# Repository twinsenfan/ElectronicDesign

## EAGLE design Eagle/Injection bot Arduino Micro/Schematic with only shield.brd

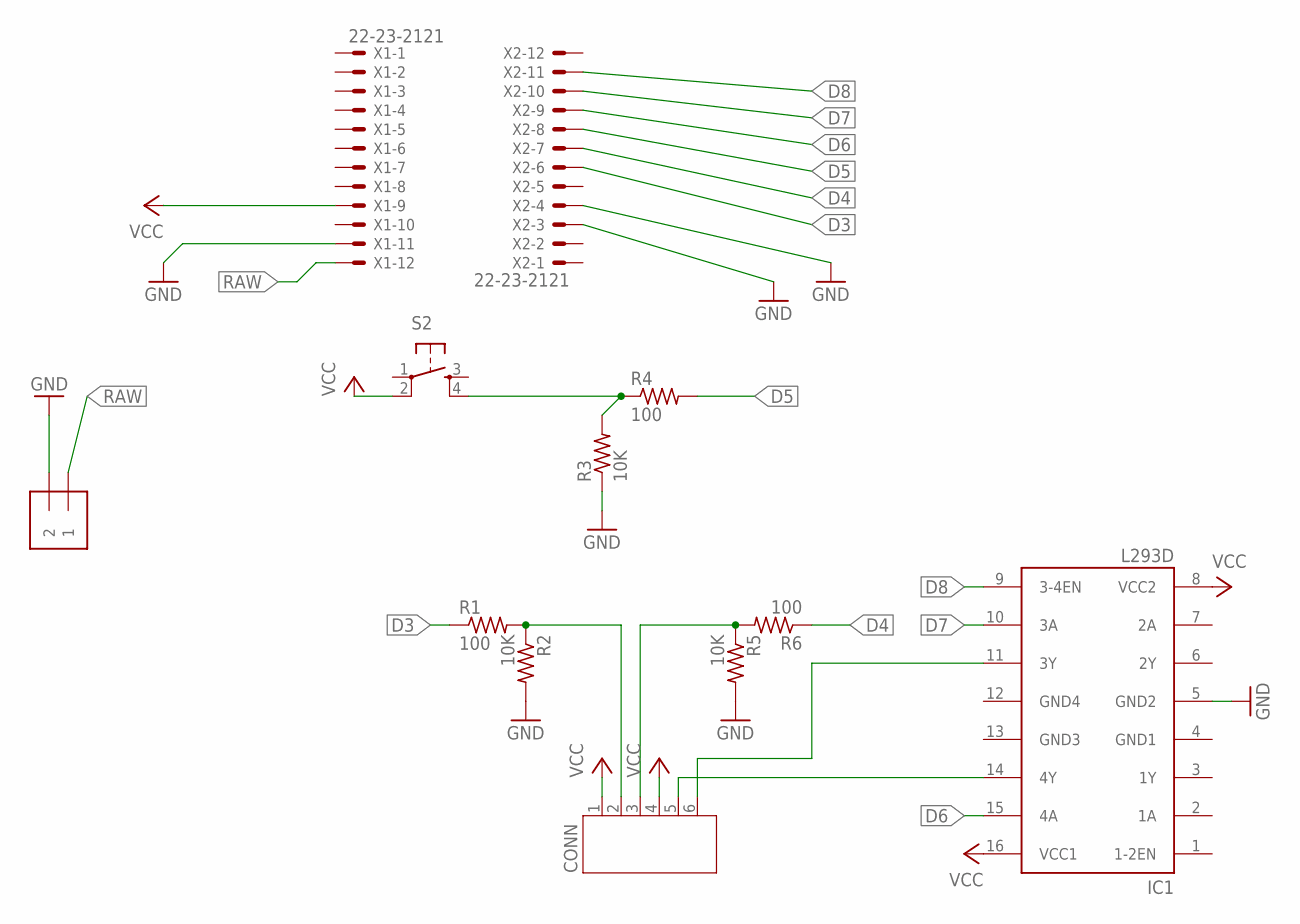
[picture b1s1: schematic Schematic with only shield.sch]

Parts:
CONN: JST-PH6
IC1: L293D; DIL16; MPN L293DNEE4
J1: 1X2-3.5MM
R1, R4, R6: 100; 0204/7; MPN 0-65-425
R2, R3, R5: 10K; 0204/7
S2: TAC_SWITCHPTH; TACTILE-PTH
X1, X2: 22-23-2121

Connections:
D3: R1.1, X2.6
D4: R6.1, X2.7
D5: R4.2, X2.8
D6: IC1.15 (4A), X2.9
D7: IC1.10 (3A), X2.10
D8: IC1.9 (3-4EN), X2.11
GND: IC1.5 (GND2), J1.2, R2.2, R3.1, R5.2, X1.11, X2.3, X2.4
GND1: IC1.4 (GND1)
GND3: IC1.13 (GND3)
GND4: IC1.12 (GND4)
unnamed: R3.2, R4.1, S2.4
unnamed: CONN.3, R5.1, R6.2
unnamed: CONN.2, R1.2, R2.1
unnamed: CONN.6, IC1.11 (3Y)
unnamed: CONN.5, IC1.14 (4Y)
RAW: J1.1, X1.12
VCC: CONN.1, CONN.4, IC1.8 (VCC2), IC1.16 (VCC1), S2.2, X1.9

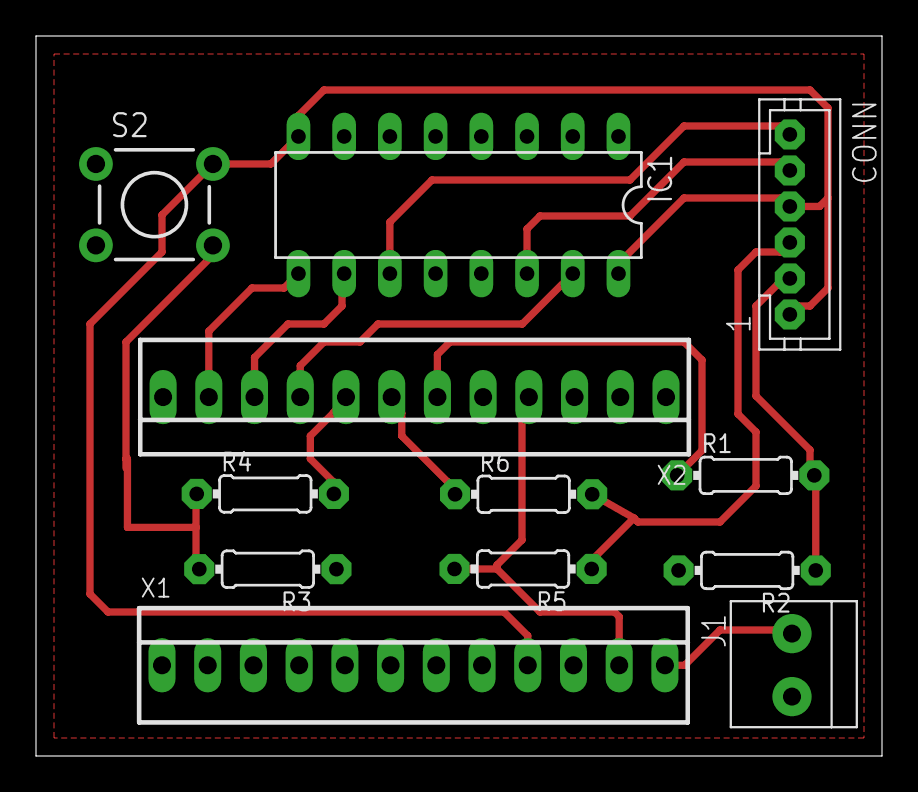
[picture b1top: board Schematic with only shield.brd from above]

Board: 2 copper layers, 47.0 x 40.0 mm, 12 parts (0 on the bottom side), 14 nets.

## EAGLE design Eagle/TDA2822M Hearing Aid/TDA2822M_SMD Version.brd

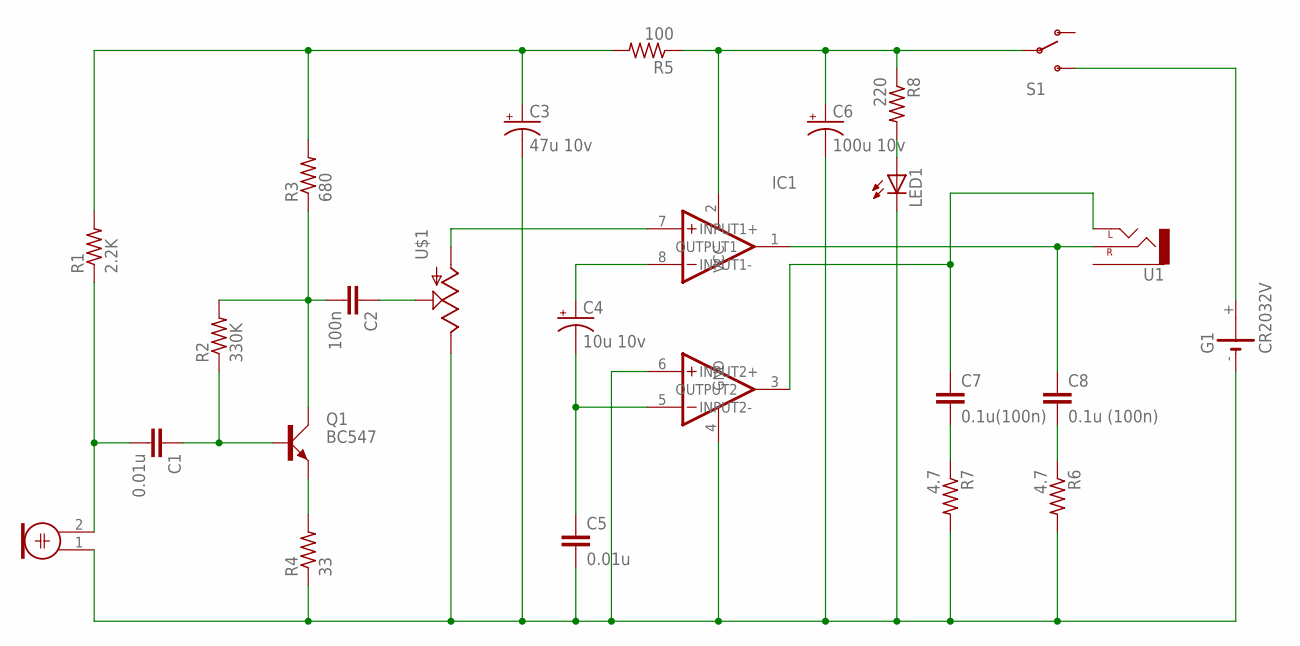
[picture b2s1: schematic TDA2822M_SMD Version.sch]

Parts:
C1, C5: 0.01u; 1206
C2: 100n; 0805
C3: 47u 10v; CPOL-RADIAL-10UF-25V
C4: 10u 10v; CPOL-RADIAL-10UF-25V
C6: 100u 10v; CPOL-RADIAL-10UF-25V
C7: 0.1u(100n); 1206
C8: 0.1u (100n); 1206
G1: CR2032V
IC1: TDA2822M; DIL8
LED1: LED3MM
M1: ELECTRET_MICROPHON-F6035AP; F6035AP
Q1: BC547; SOT54A
R1: 2.2K; R1206
R2: 330K; R1206
R3: 680; R1206
R4: 33; R1206
R5: 100; R1206
R6, R7: 4.7; R1206
R8: 220; R1206
S1: SWITCH-SPSTKIT; SWITCH-SPDT_KIT
U1: AUDIO-JACKPTH; AUDIO-JACK
U$1: POT-RV16AF-20; POT_ALPHA_RV16AF-20

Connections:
GND: C3.2 (-), C5.2, C6.2 (-), G1.-, IC1.4 (GND), IC1.6 (INPUT2+), LED1.K (C), M1.1, R4.1, R6.2, R7.2, U$1.3 (E)
unnamed: C3.1 (+), R1.2, R3.2, R5.2
unnamed: C2.2, Q1.C, R2.2, R3.1
unnamed: C1.2, M1.2, R1.1
unnamed: Q1.E, R4.2
unnamed: C2.1, U$1.2 (S)
unnamed: C4.2 (-), C5.1, IC1.5 (INPUT2-)
unnamed: C7.2, R7.1
unnamed: C8.2, R6.1
unnamed: LED1.A, R8.2
unnamed: C6.1 (+), IC1.2 (VCC), R5.1, R8.1, S1.2
unnamed: C8.1, IC1.1 (OUTPUT1), U1.RING (RIGHT)
unnamed: C1.1, Q1.B, R2.1
unnamed: C4.1 (+), IC1.8 (INPUT1-)
unnamed: IC1.7 (INPUT1+), U$1.1 (A)
unnamed: C7.1, IC1.3 (OUTPUT2), U1.TIP (LEFT)
VCC: G1.+, S1.3 (S)

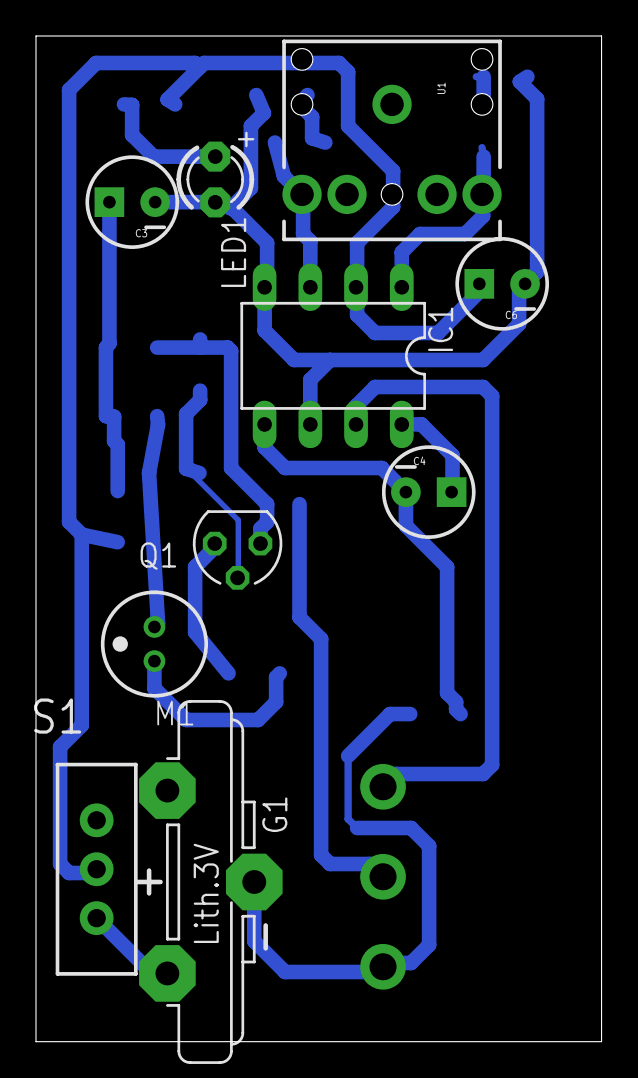
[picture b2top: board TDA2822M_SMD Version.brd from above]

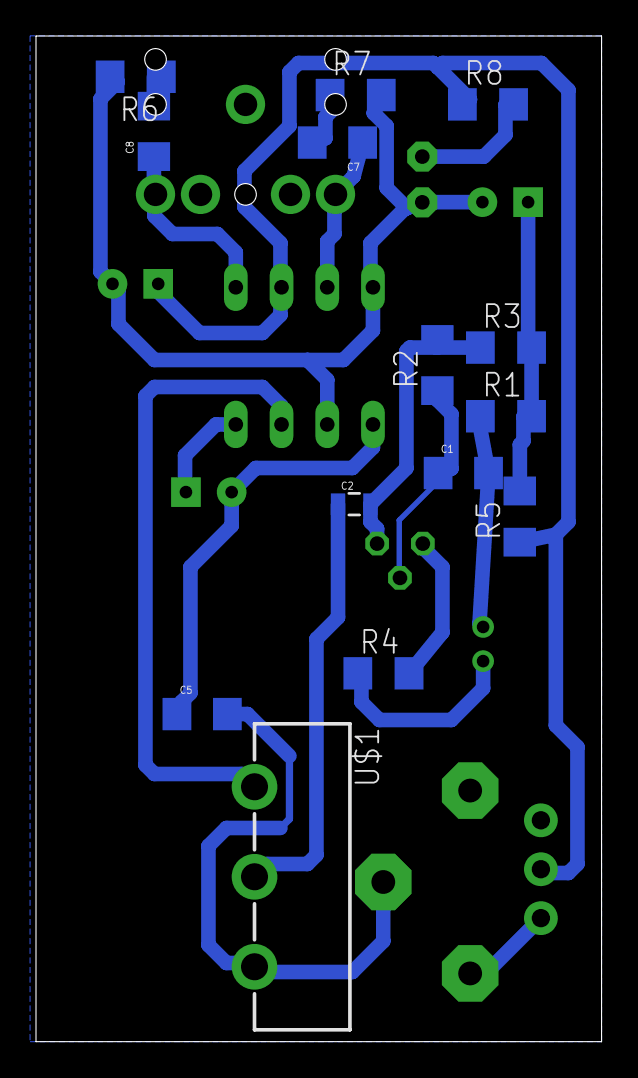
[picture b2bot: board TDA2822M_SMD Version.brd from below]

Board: 2 copper layers, 31.4 x 55.9 mm, 24 parts (14 on the bottom side), 17 nets.

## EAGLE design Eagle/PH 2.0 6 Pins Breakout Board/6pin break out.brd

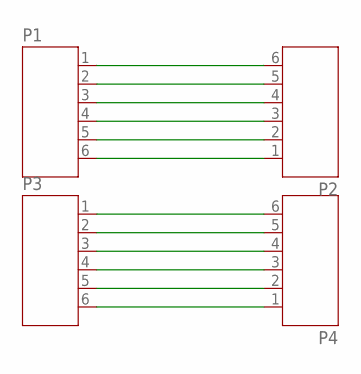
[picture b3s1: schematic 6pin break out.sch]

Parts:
P1, P2, P3, P4: JST-PH6

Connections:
unnamed: P1.1, P2.6
unnamed: P1.2, P2.5
unnamed: P1.3, P2.4
unnamed: P1.4, P2.3
unnamed: P1.5, P2.2
unnamed: P1.6, P2.1
unnamed: P3.1, P4.6
unnamed: P3.2, P4.5
unnamed: P3.3, P4.4
unnamed: P3.4, P4.3
unnamed: P3.5, P4.2
unnamed: P3.6, P4.1

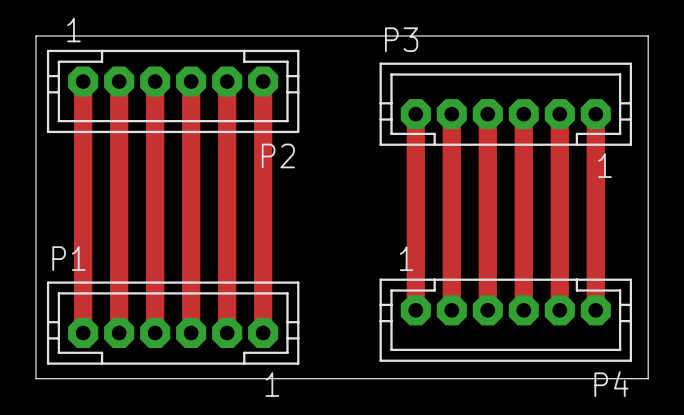
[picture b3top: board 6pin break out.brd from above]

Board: 2 copper layers, 34.0 x 19.0 mm, 4 parts (0 on the bottom side), 12 nets.

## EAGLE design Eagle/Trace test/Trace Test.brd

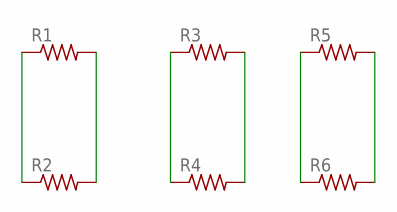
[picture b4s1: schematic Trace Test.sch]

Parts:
R1, R2, R3, R4, R5, R6: R-US_0204/5; 0204/5

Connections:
unnamed: R1.1, R2.1
unnamed: R1.2, R2.2
unnamed: R3.1, R4.1
unnamed: R3.2, R4.2
unnamed: R5.1, R6.1
unnamed: R5.2, R6.2

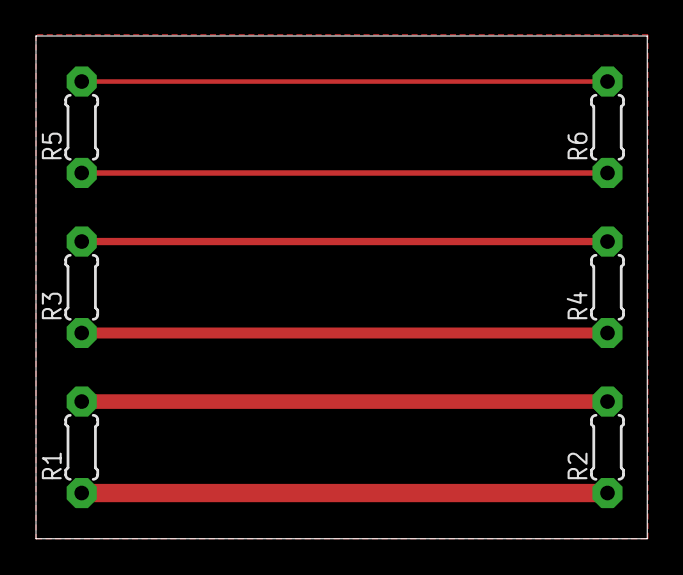
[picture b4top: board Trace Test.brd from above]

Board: 2 copper layers, 34.0 x 27.9 mm, 6 parts (0 on the bottom side), 6 nets.

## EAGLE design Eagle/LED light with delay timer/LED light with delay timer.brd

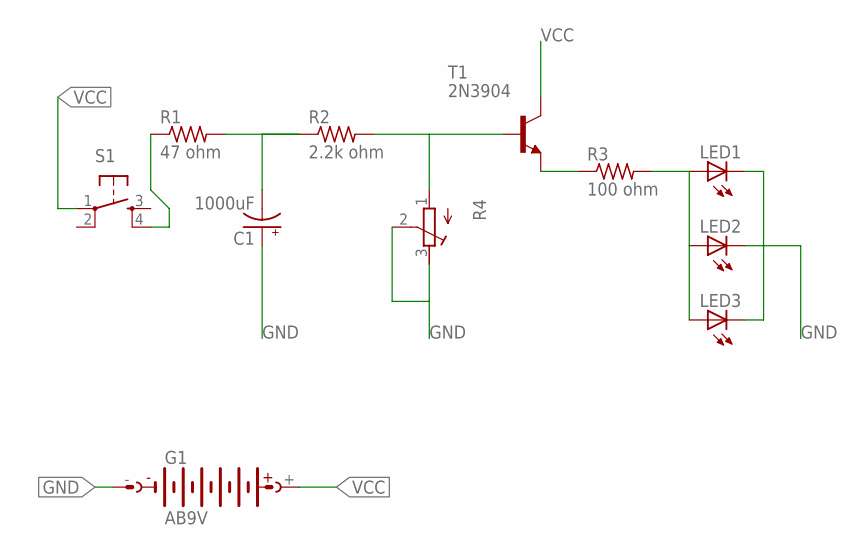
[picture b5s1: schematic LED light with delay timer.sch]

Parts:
C1: 1000uF; CPOL-RADIAL-100UF-25V
G1: AB9V
LED1, LED2, LED3: LED5MM
R1: 47 ohm; 0204/7
R2: 2.2k ohm; 0204/7
R3: 100 ohm; 0204/7
R4: R-TRIMM3339P; RTRIM3339P
S1: TAC_SWITCHPTH; TACTILE-PTH
T1: 2N3904; TO92

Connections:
GND: C1.1 (+), G1.-, LED1.K (C), LED2.K (C), LED3.K (C), R4.2 (S), R4.3 (E)
unnamed: C1.2 (-), R1.2, R2.1
unnamed: R2.2, R4.1 (A), T1.2 (B)
unnamed: R1.1, S1.4
unnamed: R3.1, T1.3 (E)
unnamed: LED1.A, LED2.A, LED3.A, R3.2
VCC: G1.+, S1.1, T1.1 (C)

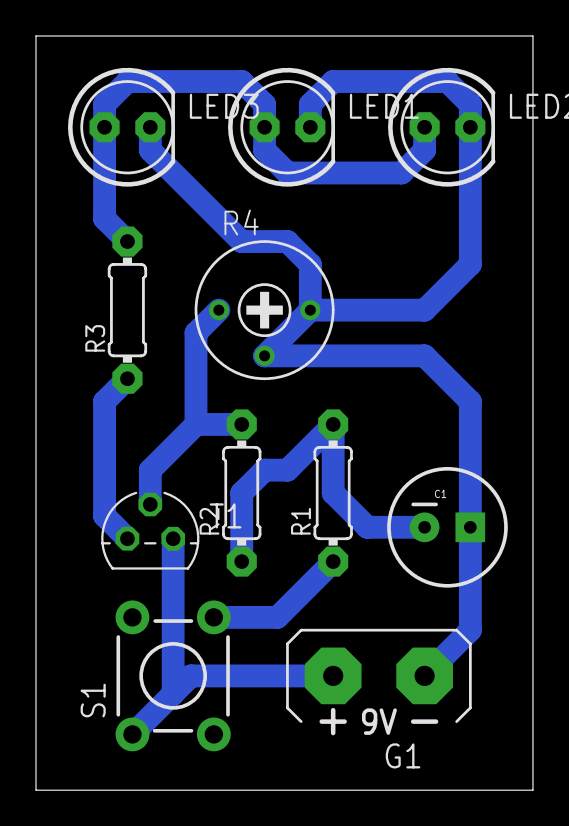
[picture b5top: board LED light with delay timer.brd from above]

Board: 2 copper layers, 27.6 x 41.9 mm, 11 parts (0 on the bottom side), 7 nets.

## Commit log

2014-08-17 :confetti_ball: Added .gitattributes & .gitignore files
2014-08-17 Upload all designs
    Syncing all to GitHub
2014-08-17 Clean up the folder
2019-02-26 Create DigiSpark
2019-02-26 Initial upload of DigidSpark
    Initial upload of DigidSpark

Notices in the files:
parts and their libraries:
SparkFun: Licensing: CC v3.0 Share-Alike You are welcome to use this library for commercial purposes.
